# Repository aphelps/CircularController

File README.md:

This design uses:

* Adafruit Lipo Charger: https://www.adafruit.com/products/259
  - https://learn.adafruit.com/li-ion-and-lipoly-batteries/downloads

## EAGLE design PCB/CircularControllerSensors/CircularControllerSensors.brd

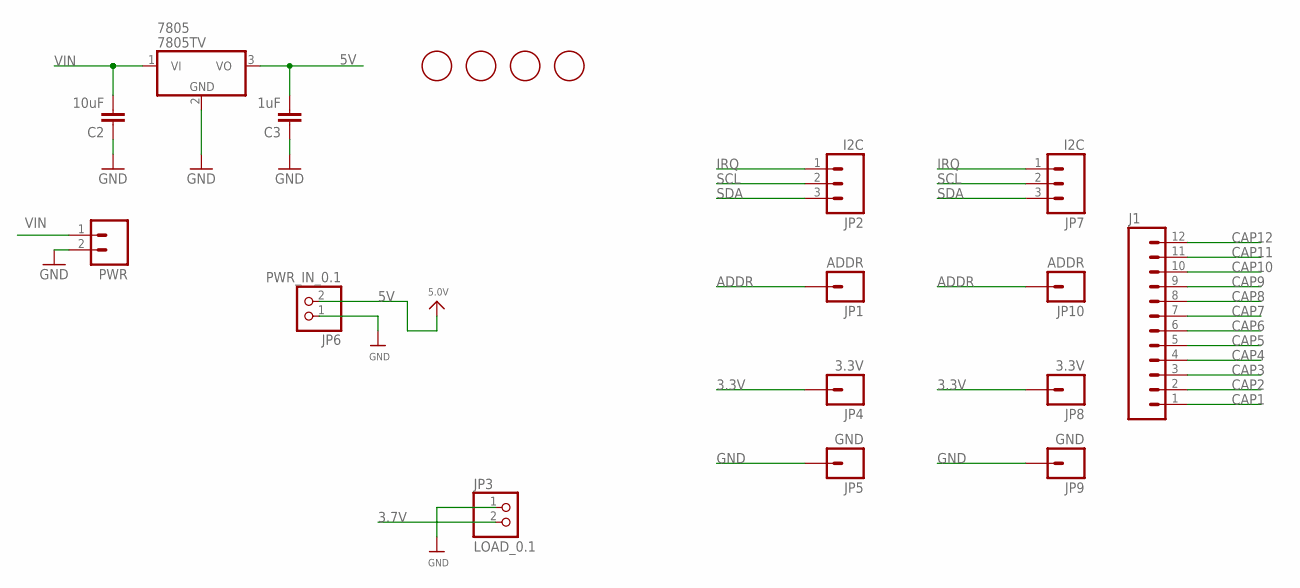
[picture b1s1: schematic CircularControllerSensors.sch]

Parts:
7805: 7805TV; TO220V
C2: 10uF; 1206
C3: 1uF; 1206
J1: M12PTH; 1X12
JP1, JP10: ADDR; 1X01
JP2, JP7: I2C; 1X03
JP3: LOAD_0.1; 1X02_OVAL
JP4, JP8: 3.3V; 1X01
JP5, JP9: GND; 1X01
JP6: PWR_IN_0.1; 1X02_OVAL
PWR: M025MM; SCREWTERMINAL-5MM-2
U$11, U$16, U$18, U$19: MOUNTINGHOLE2.0; MOUNTINGHOLE_2.0_PLATED

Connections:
3.3V: JP4.1, JP8.1
3.7V: JP3.2
5V: 7805.3 (VO), C3.2, JP6.2
ADDR: JP1.1, JP10.1
CAP1: J1.1
CAP2: J1.2
CAP3: J1.3
CAP4: J1.4
CAP5: J1.5
CAP6: J1.6
CAP7: J1.7
CAP8: J1.8
CAP9: J1.9
CAP10: J1.10
CAP11: J1.11
CAP12: J1.12
GND: 7805.2 (GND), C2.1, C3.1, JP3.1, JP5.1, JP6.1, JP9.1, PWR.2
IRQ: JP2.1, JP7.1
SCL: JP2.2, JP7.2
SDA: JP2.3, JP7.3
VIN: 7805.1 (VI), C2.2, PWR.1

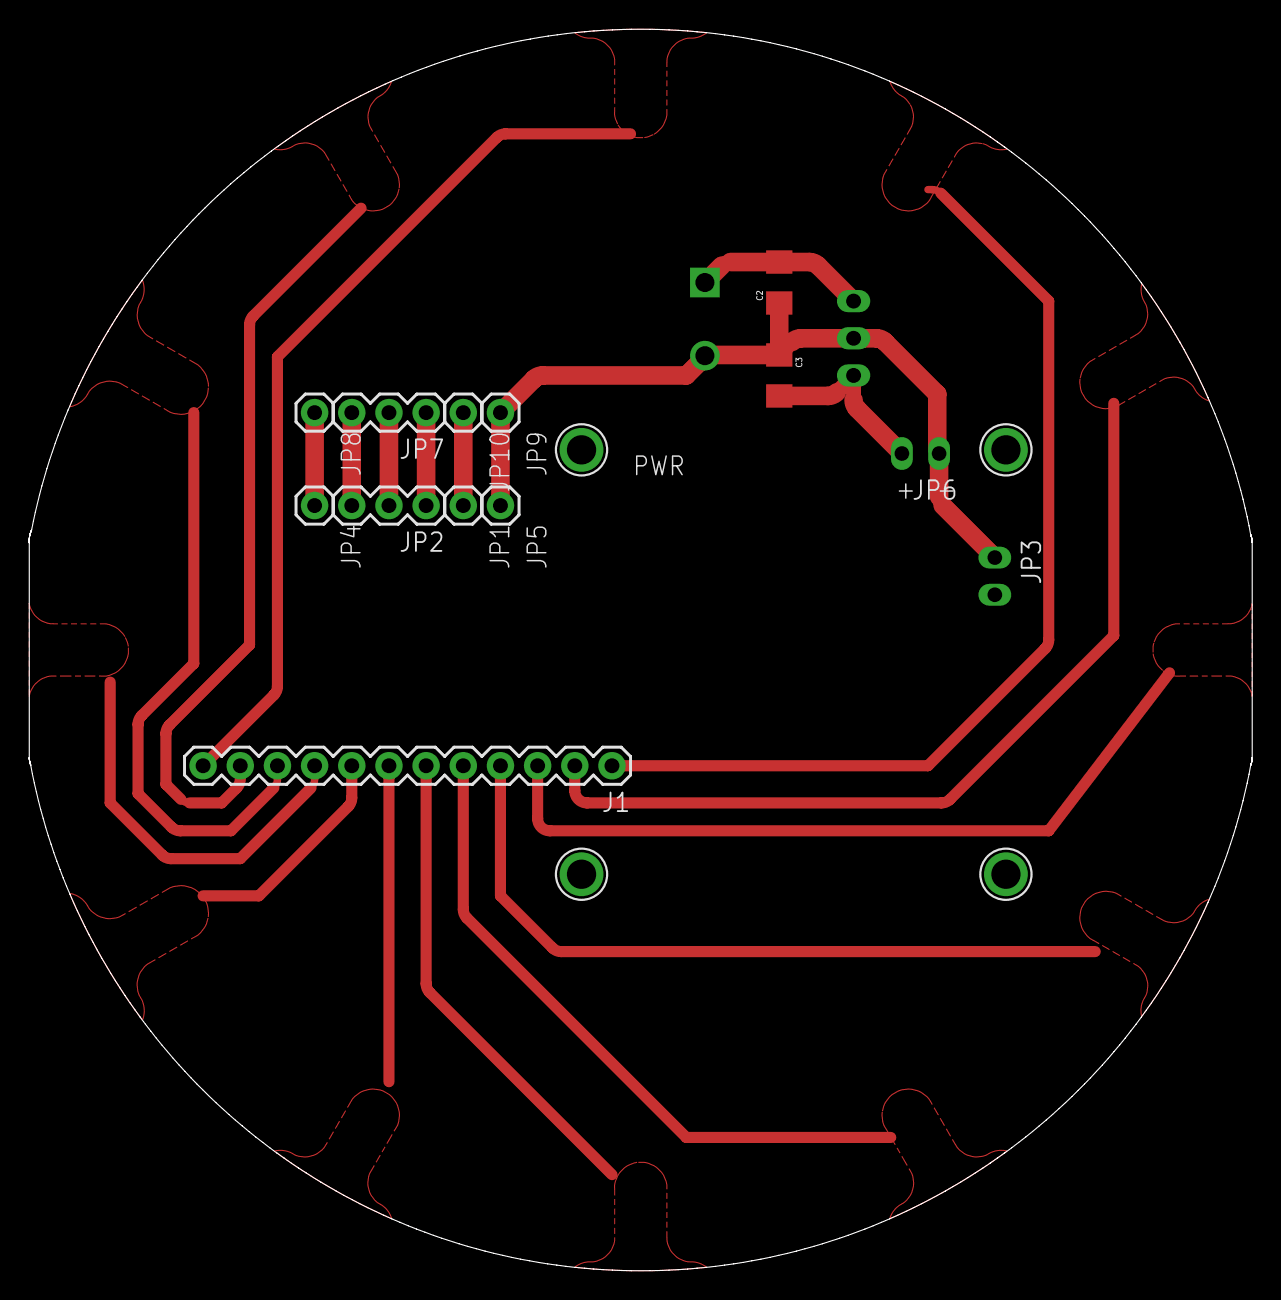
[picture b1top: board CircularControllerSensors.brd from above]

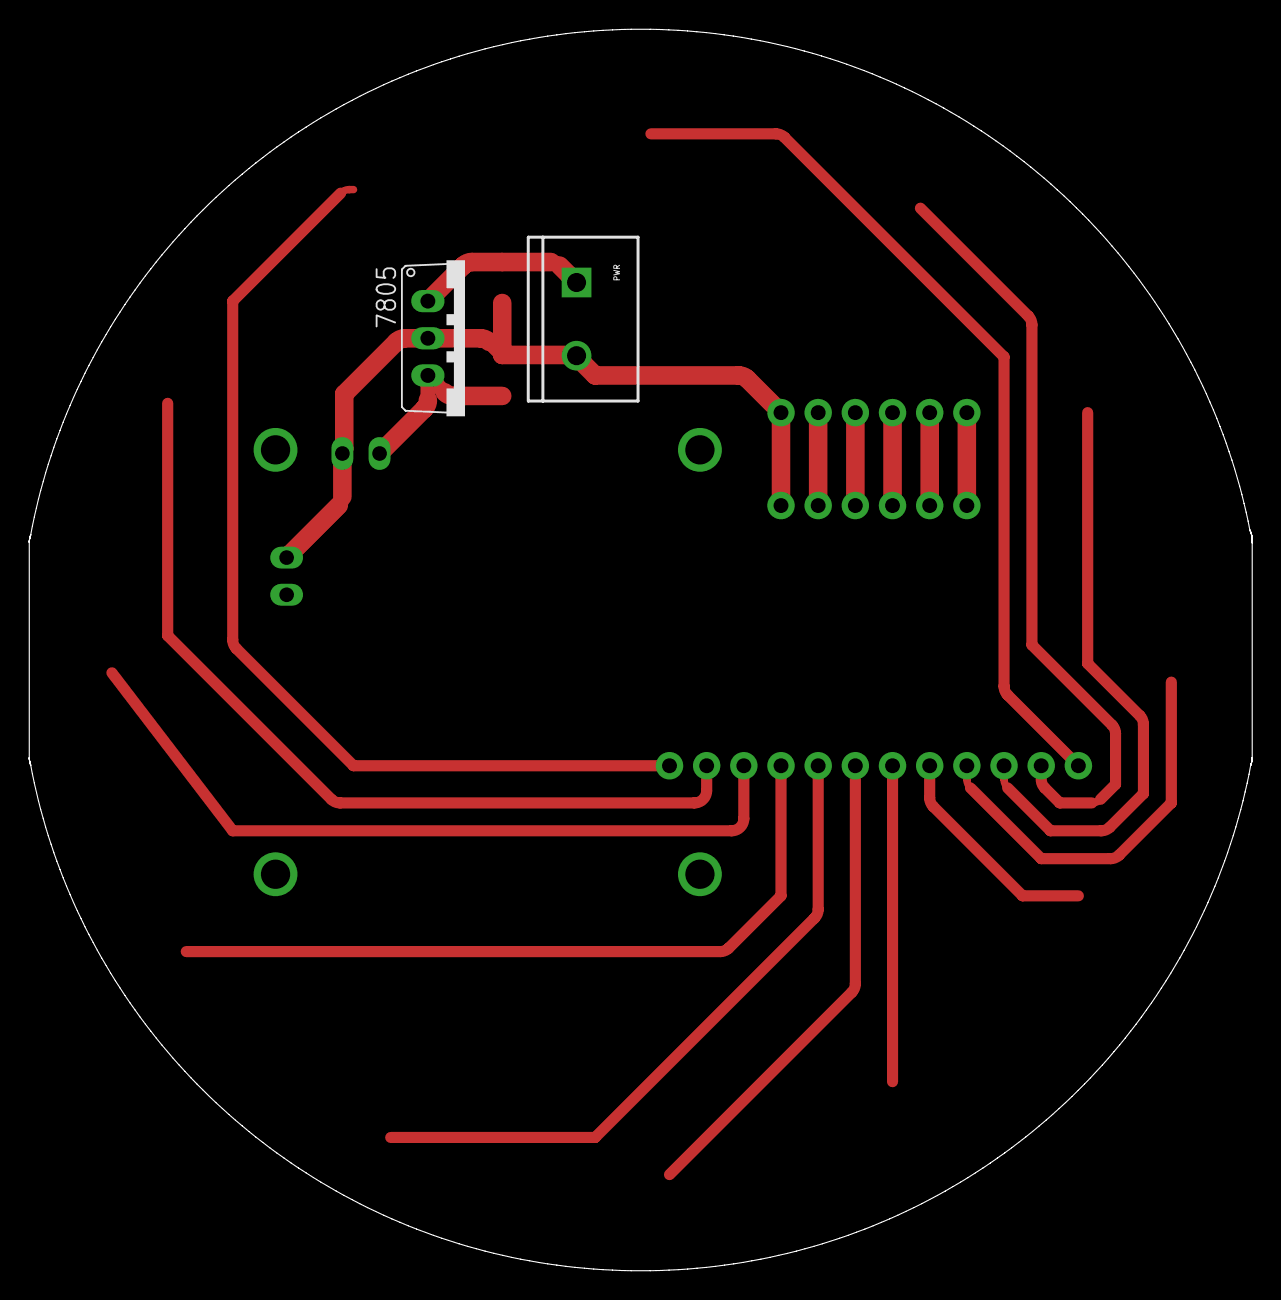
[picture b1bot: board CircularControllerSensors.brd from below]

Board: 2 copper layers, 83.6 x 84.8 mm, 19 parts (2 on the bottom side), 8 nets.

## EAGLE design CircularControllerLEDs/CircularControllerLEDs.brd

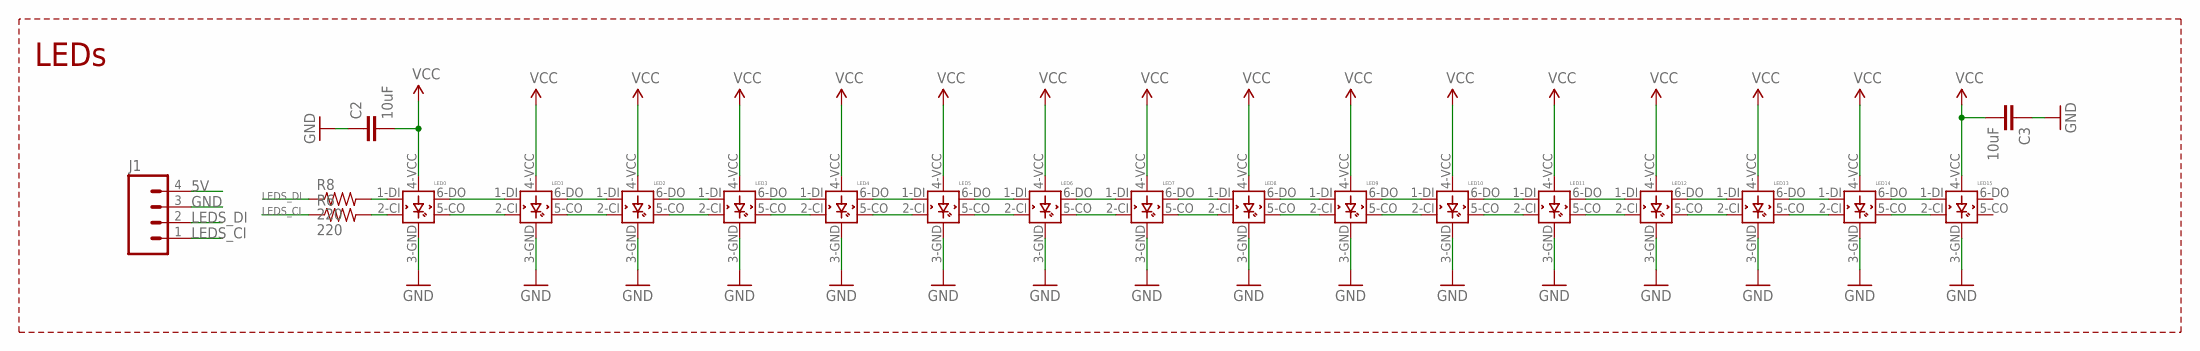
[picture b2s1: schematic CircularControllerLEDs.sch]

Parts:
C2, C3: 10uF; 1206
J1: M04PTH; 1X04
LED0, LED1, LED2, LED3, LED4, LED5, LED6, LED7, LED8, LED9, LED10, LED11, LED12, LED13, LED14, LED15: APA102; 5050
R6, R8: 220; 0603-RES@1

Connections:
5V: C2.2, J1.4, LED0.4-VCC (VCC)
GND: C2.1, C3.1, J1.3, LED0.3-GND (GND), LED1.3-GND (GND), LED2.3-GND (GND), LED3.3-GND (GND), LED4.3-GND (GND), LED5.3-GND (GND), LED6.3-GND (GND), LED7.3-GND (GND), LED8.3-GND (GND), LED9.3-GND (GND), LED10.3-GND (GND), LED11.3-GND (GND), LED12.3-GND (GND), LED13.3-GND (GND), LED14.3-GND (GND), LED15.3-GND (GND)
LEDS_CI: J1.1, R6.1
LEDS_DI: J1.2, R8.1
unnamed: LED0.1-DI (DI), R8.2
unnamed: LED0.6-DO (DO), LED1.1-DI (DI)
unnamed: LED0.2-CI (CI), R6.2
unnamed: LED0.5-CO (CO), LED1.2-CI (CI)
unnamed: LED1.6-DO (DO), LED2.1-DI (DI)
unnamed: LED1.5-CO (CO), LED2.2-CI (CI)
unnamed: LED2.6-DO (DO), LED3.1-DI (DI)
unnamed: LED2.5-CO (CO), LED3.2-CI (CI)
unnamed: LED3.5-CO (CO), LED4.2-CI (CI)
unnamed: LED3.6-DO (DO), LED4.1-DI (DI)
unnamed: LED4.6-DO (DO), LED5.1-DI (DI)
unnamed: LED4.5-CO (CO), LED5.2-CI (CI)
unnamed: LED5.6-DO (DO), LED6.1-DI (DI)
unnamed: LED5.5-CO (CO), LED6.2-CI (CI)
unnamed: LED6.6-DO (DO), LED7.1-DI (DI)
unnamed: LED6.5-CO (CO), LED7.2-CI (CI)
unnamed: LED7.5-CO (CO), LED8.2-CI (CI)
unnamed: LED7.6-DO (DO), LED8.1-DI (DI)
unnamed: LED8.6-DO (DO), LED9.1-DI (DI)
unnamed: LED8.5-CO (CO), LED9.2-CI (CI)
unnamed: LED9.6-DO (DO), LED10.1-DI (DI)
unnamed: LED9.5-CO (CO), LED10.2-CI (CI)
unnamed: LED10.6-DO (DO), LED11.1-DI (DI)
unnamed: LED10.5-CO (CO), LED11.2-CI (CI)
unnamed: LED11.6-DO (DO), LED12.1-DI (DI)
unnamed: LED11.5-CO (CO), LED12.2-CI (CI)
unnamed: LED12.6-DO (DO), LED13.1-DI (DI)
unnamed: LED12.5-CO (CO), LED13.2-CI (CI)
unnamed: LED13.6-DO (DO), LED14.1-DI (DI)
unnamed: LED13.5-CO (CO), LED14.2-CI (CI)
unnamed: LED14.6-DO (DO), LED15.1-DI (DI)
unnamed: LED14.5-CO (CO), LED15.2-CI (CI)
VCC: C3.2, LED1.4-VCC (VCC), LED2.4-VCC (VCC), LED3.4-VCC (VCC), LED4.4-VCC (VCC), LED5.4-VCC (VCC), LED6.4-VCC (VCC), LED7.4-VCC (VCC), LED8.4-VCC (VCC), LED9.4-VCC (VCC), LED10.4-VCC (VCC), LED11.4-VCC (VCC), LED12.4-VCC (VCC), LED13.4-VCC (VCC), LED14.4-VCC (VCC), LED15.4-VCC (VCC)

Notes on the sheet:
LEDs

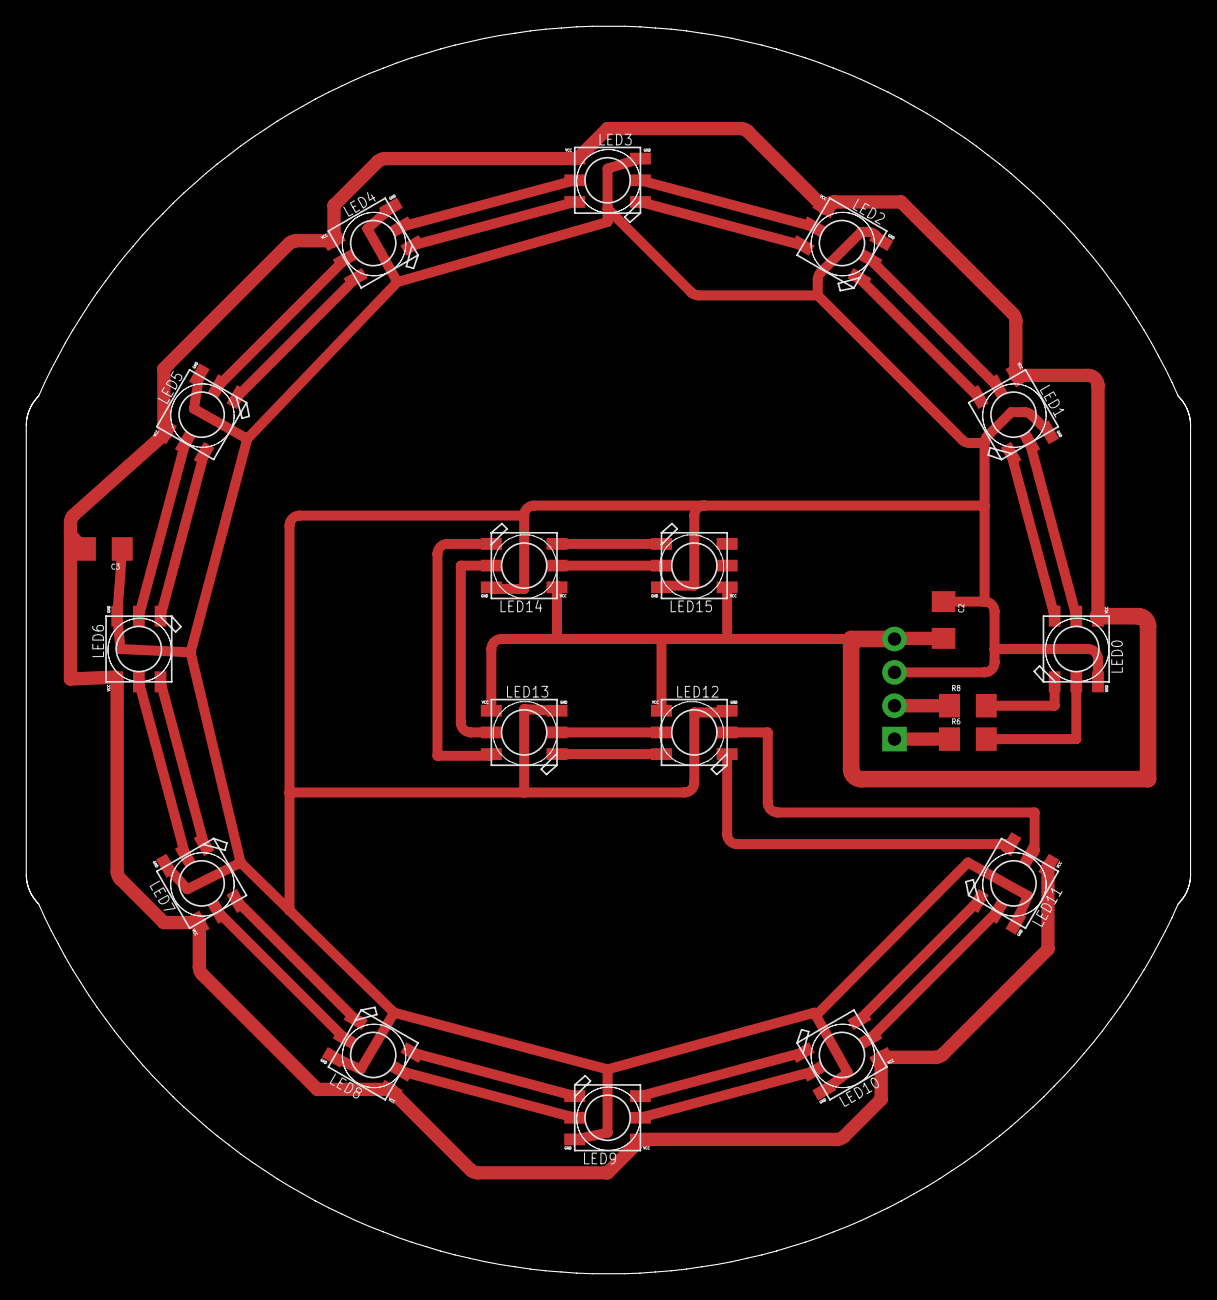
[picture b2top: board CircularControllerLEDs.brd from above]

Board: 2 copper layers, 88.6 x 95.0 mm, 21 parts (1 on the bottom side), 37 nets.

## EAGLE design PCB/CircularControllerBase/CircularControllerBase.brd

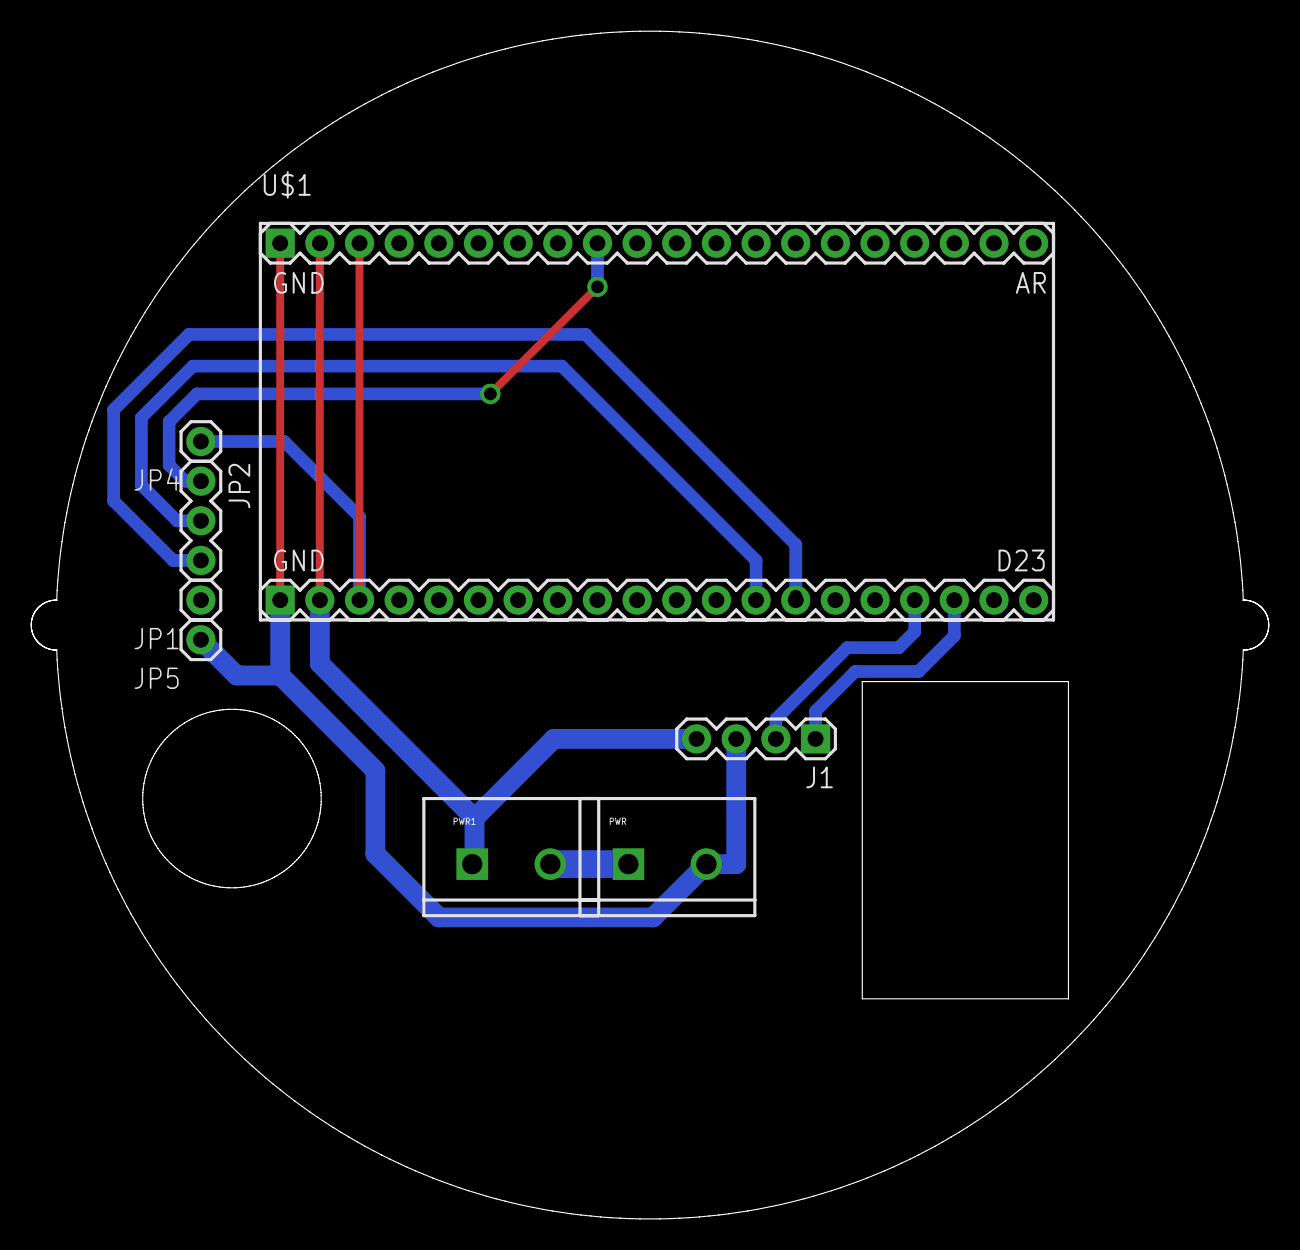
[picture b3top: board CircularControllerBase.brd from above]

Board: 2 copper layers, 79.3 x 76.1 mm, 8 parts (0 on the bottom side), 9 nets.

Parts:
J1: 1X04
JP1: ADDR; 1X01
JP2: I2C; 1X03
JP4: 3.3V; 1X01
JP5: GND; 1X01
PWR, PWR1: SCREWTERMINAL-5MM-2
U$1: MOTEINO_MEGA_MODULE; MEGA_SQ

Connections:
3.3V: JP4.1, U$1.3, U$1.23
3.7V: J1.4, PWR1.1, U$1.2, U$1.22
BAT+: PWR.1, PWR1.2
GND: J1.3, JP5.1, PWR.2, U$1.1, U$1.21
IRQ: JP2.1, U$1.9
LEDS_CI: J1.1, U$1.38
LEDS_DI: J1.2, U$1.37
SCL: JP2.2, U$1.33
SDA: JP2.3, U$1.34

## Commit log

2017-02-05 Updated PCBs
2017-02-05 Initial version of the circular controller PCB
2017-02-05 Circular Controller PCBs
2017-02-05 Added Bringup script
2017-02-12 Added RFM69 to Bringup script
2017-02-16 Initial compiling non-functional controller code
2018-01-21 Moved PCBs into subdirectory
2026-04-12 Old changes...
2026-04-13 Added Makefile with Claude
2026-04-13 Updated gitignore

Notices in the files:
parts and their libraries:
SparkFun-Resistors: Licensing: Creative Commons ShareAlike 4.0 International - https://creativecommons.org/licenses/by-sa/4.0
